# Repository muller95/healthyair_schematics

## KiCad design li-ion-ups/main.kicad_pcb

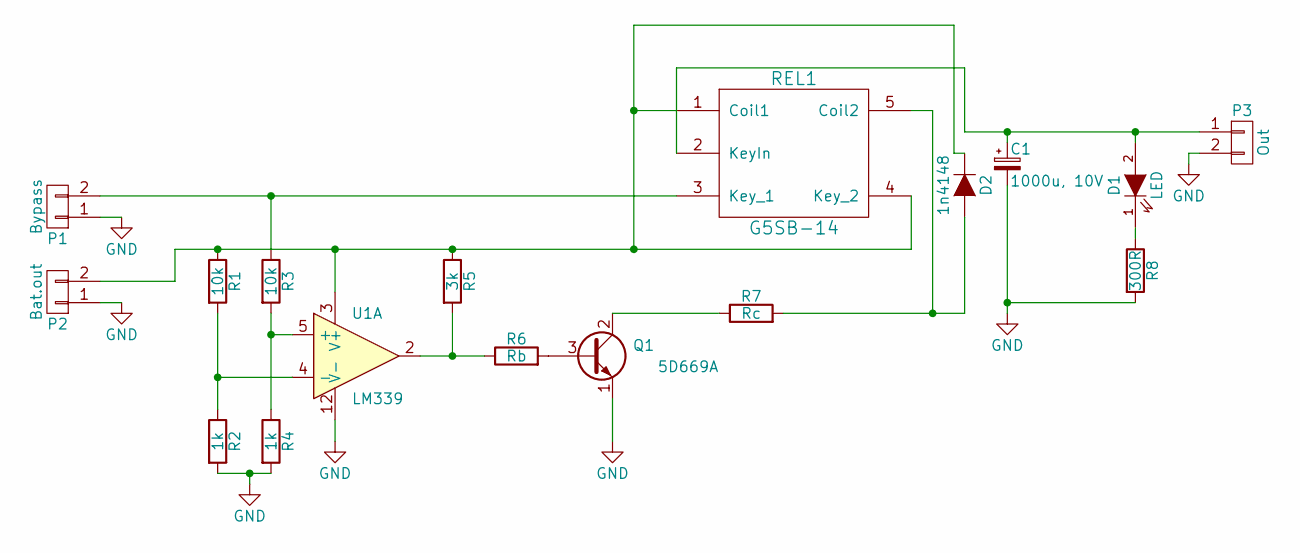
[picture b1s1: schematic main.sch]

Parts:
C1: 1000u, 10V; C1.5V8V
D1: LED; LED-3MM
D2: 1n4148; Diode_DO-35_SOD27_Horizontal_RM10
P1: Bypass; Pin_Header_Straight_1x02
P2: Bat.out; Pin_Header_Straight_1x02
P3: Out; Pin_Header_Straight_1x02
Q1: 5D669A; TO-220_Neutral123_Vertical
R1, R3: 10k; R3
R2, R4: 1k; R3
R5: 3k; R3
R6: Rb; R3
R7: Rc; R3
R8: 300R; R3
REL1: G5SB-14; Relay_SPDS_OMRON-G6E
U1: LM339; DIP-14_W7.62mm_LongPads

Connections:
GND: C1.2, P1.1, P2.1, P3.2, Q1.1 (E), R2.2, R4.2, R8.2, U1.12 (V-)
unnamed: C1.1, D1.2 (A), P3.1, REL1.2 (KeyIn)
unnamed: D1.1 (K), R8.1
unnamed: D2.1 (K), P2.2, R1.1, R5.1, REL1.1 (Coil1), REL1.4 (Key_2), U1.3 (V+)
unnamed: D2.2 (A), R7.2, REL1.5 (Coil2)
unnamed: P1.2, R3.1, REL1.3 (Key_1)
unnamed: Q1.2 (C), R7.1
unnamed: Q1.3 (B), R6.2
unnamed: R1.2, R2.1, U1.4 (-)
unnamed: R3.2, R4.1, U1.5 (+)
unnamed: R5.2, R6.1, U1.2

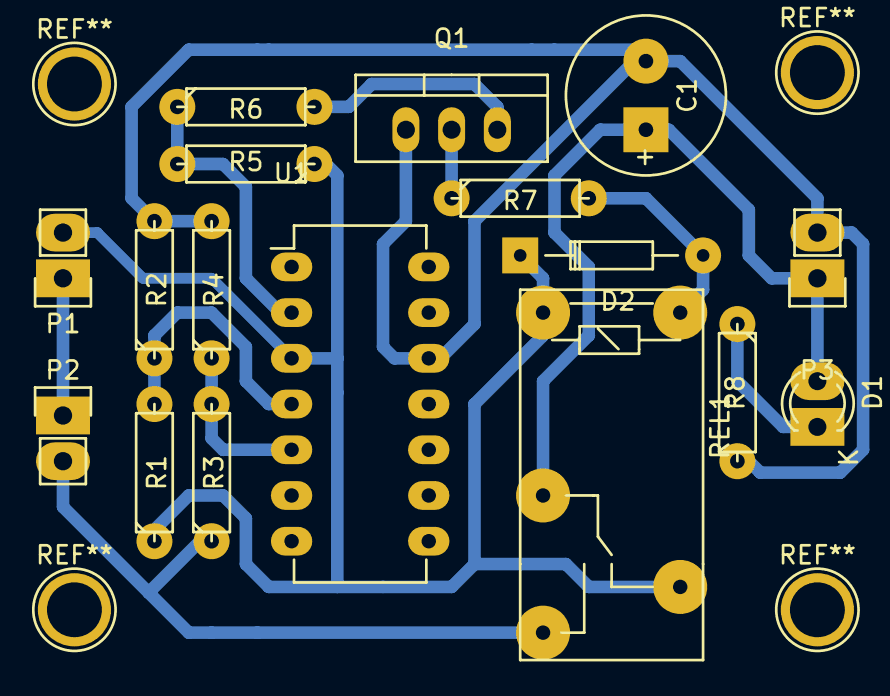
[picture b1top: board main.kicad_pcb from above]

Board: 2 copper layers, 17 parts (0 on the bottom side), 11 nets.

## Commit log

2017-06-15 Первый коммит
    Загрузил проект ИБП
